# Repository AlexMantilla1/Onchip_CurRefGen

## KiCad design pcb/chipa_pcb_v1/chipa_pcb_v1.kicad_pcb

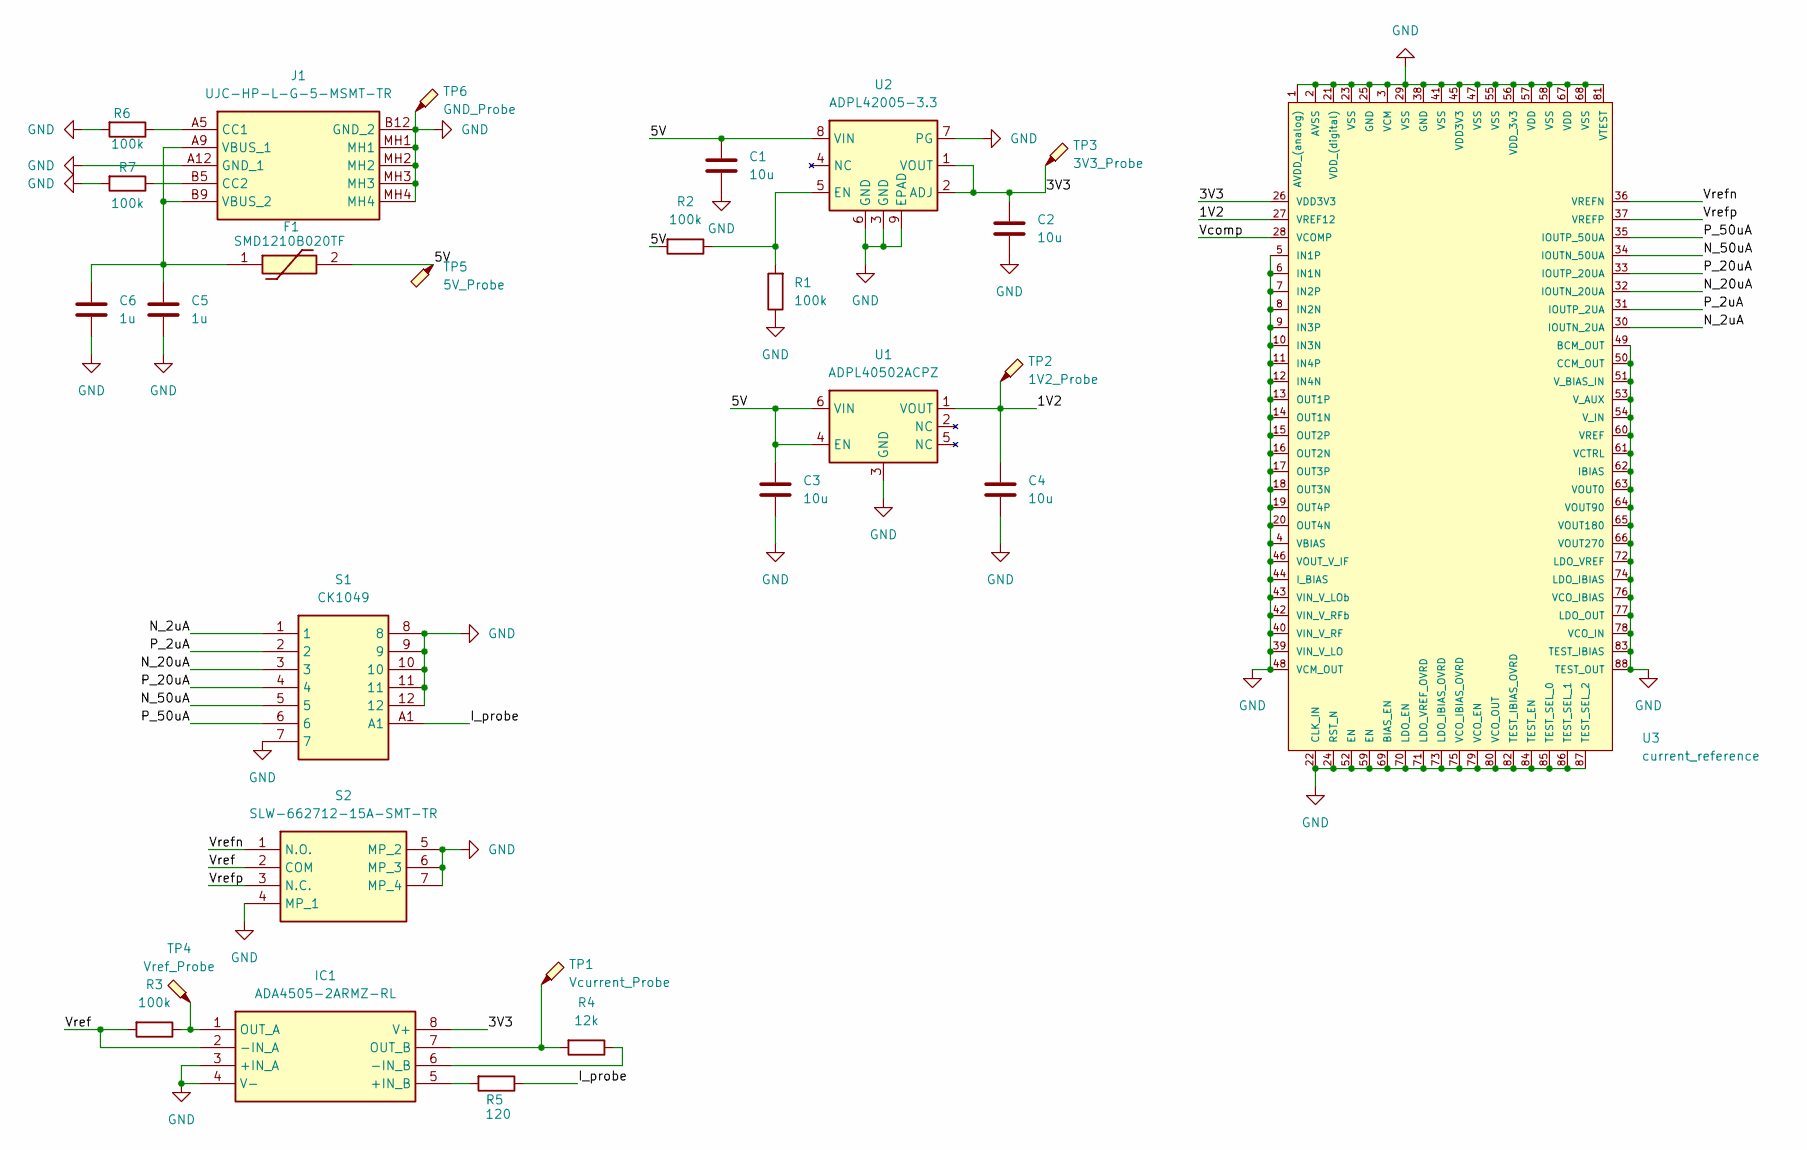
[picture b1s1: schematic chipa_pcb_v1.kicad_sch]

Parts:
C1, C2, C3, C4: 10u; C_0201_0603Metric
C5, C6: 1u; C_0201_0603Metric
F1: SMD1210B020TF; FUSC3226X110N; Mouser Part Number 603-SMD1210B020TF
IC1: ADA4505-2ARMZ-RL; SOP65P490X110-8N; Mouser Part Number 584-ADA4505-2ARMZ-R
J1: UJC-HP-L-G-5-MSMT-TR; UJCHPLG5MSMTTR; Mouser Part Number 179-UJCHPLG5MSMTTR
R1, R2, R3, R6, R7: 100k; R_0603_1608Metric
R4: 12k; R_0603_1608Metric
R5: 120; R_0603_1608Metric
S1: CK1049; CK1059; Mouser Part Number 105-CK1049
S2: SLW-662712-15A-SMT-TR; SLW66271215ASMTTR; Manufacturer_Part_Number SLW-662712-15A-SMT-TR
TP1: Vcurrent_Probe; TestPoint_Pad_4.0x4.0mm
TP2: 1V2_Probe; TestPoint_Pad_4.0x4.0mm
TP3: 3V3_Probe; TestPoint_Pad_4.0x4.0mm
TP4: Vref_Probe; TestPoint_Pad_4.0x4.0mm
TP5: 5V_Probe; TestPoint_Pad_4.0x4.0mm
TP6: GND_Probe; TestPoint_Pad_4.0x4.0mm
U1: ADPL40502ACPZ; LFCSP-6-1EP_2x2mm_P0.65mm_EP1x1.6mm
U2: ADPL42005-3.3; LFCSP-WD-8-1EP_3x3mm_P0.65mm_EP1.6x2.44mm
U3: current_reference; QFN-88_EP_10x10_Pitch0.4mm

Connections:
/1V2: C4.1, TP2.1 (1_1), U1.1 (VOUT), U3.27 (VREF12)
/3V3: C2.1, IC1.8 (V+), TP3.1 (1_1), U2.1 (VOUT), U2.2 (ADJ), U3.26 (VDD3V3)
/5V: C1.1, C3.1, F1.2, R2.2, TP5.1 (1_1), U1.4 (EN), U1.6 (VIN), U2.8 (VIN)
/I_probe: R5.1, S1.A1
/N_2uA: S1.1, U3.30 (IOUTN_2UA)
/N_20uA: S1.3, U3.32 (IOUTN_20UA)
/N_50uA: S1.5, U3.34 (IOUTN_50UA)
/P_2uA: S1.2, U3.31 (IOUTP_2UA)
/P_20uA: S1.4, U3.33 (IOUTP_20UA)
/P_50uA: S1.6, U3.35 (IOUTP_50UA)
/Vcomp: U3.28 (VCOMP)
/Vref: IC1.2 (-IN_A), R3.2, S2.2 (COM)
/Vrefn: S2.1 (N.O.), U3.36 (VREFN)
/Vrefp: S2.3 (N.C.), U3.37 (VREFP)
GND: C1.2, C2.2, C3.2, C4.2, C5.2, C6.2, IC1.3 (+IN_A), IC1.4 (V-), J1.A12 (GND_1), J1.B12 (GND_2), J1.MH1, J1.MH2, J1.MH3, J1.MH4, R1.1, R6.2, R7.2, S1.7, S1.8, S1.9, S1.10, S1.11, S1.12, S2.4 (MP_1), S2.5 (MP_2), S2.6 (MP_3), S2.7 (MP_4), TP6.1 (1_1), U1.3 (GND), U1.7 (GND), U2.3 (GND), U2.6 (GND), U2.7 (PG), U2.9 (EPAD), U3.1 (AVDD_(analog)), U3.2 (AVSS), U3.3 (VCM), U3.4 (VBIAS), U3.5 (IN1P), U3.6 (IN1N), U3.7 (IN2P), U3.8 (IN2N), U3.9 (IN3P), U3.10 (IN3N), U3.11 (IN4P), U3.12 (IN4N), U3.13 (OUT1P), U3.14 (OUT1N), U3.15 (OUT2P), U3.16 (OUT2N), U3.17 (OUT3P), U3.18 (OUT3N), U3.19 (OUT4P), U3.20 (OUT4N), U3.21 (VDD_(digital)), U3.22 (CLK_IN), U3.23 (VSS), U3.24 (RST_N), U3.25 (GND), U3.29 (VSS), U3.38 (GND), U3.39 (VIN_V_LO), U3.40 (VIN_V_RF), U3.41 (VSS), U3.42 (VIN_V_RFb), U3.43 (VIN_V_LOb), U3.44 (I_BIAS), U3.45 (VDD3V3), U3.46 (VOUT_V_IF), U3.47 (VSS), U3.48 (VCM_OUT), U3.49 (BCM_OUT), U3.50 (CCM_OUT), U3.51 (V_BIAS_IN), U3.52 (EN), U3.53 (V_AUX), U3.54 (V_IN), U3.55 (VSS), U3.56 (VDD_3v3), U3.57 (VDD), U3.58 (VSS), U3.59 (EN), U3.60 (VREF), U3.61 (VCTRL), U3.62 (IBIAS), U3.63 (VOUT0), U3.64 (VOUT90), U3.65 (VOUT180), U3.66 (VOUT270), U3.67 (VDD), U3.68 (VSS), U3.69 (BIAS_EN), U3.70 (LDO_EN), U3.71 (LDO_VREF_OVRD), U3.72 (LDO_VREF), U3.73 (LDO_IBIAS_OVRD), U3.74 (LDO_IBIAS), U3.75 (VCO_IBIAS_OVRD), U3.76 (VCO_IBIAS), U3.77 (LDO_OUT), U3.78 (VCO_IN), U3.79 (VCO_EN), U3.80 (VCO_OUT), U3.81 (VTEST), U3.82 (TEST_IBIAS_OVRD), U3.83 (TEST_IBIAS), U3.84 (TEST_EN), U3.85 (TEST_SEL_0), U3.86 (TEST_SEL_1), U3.87 (TEST_SEL_2), U3.88 (TEST_OUT)
unnamed: IC1.5 (+IN_B), R5.2
unnamed: IC1.6 (-IN_B), R4.1
unnamed: IC1.1 (OUT_A), R3.1, TP4.1 (1_1)
unnamed: IC1.7 (OUT_B), R4.2, TP1.1 (1_1)
unnamed: J1.A5 (CC1), R6.1
unnamed: J1.B5 (CC2), R7.1
unnamed: C5.1, C6.1, F1.1, J1.A9 (VBUS_1), J1.B9 (VBUS_2)
unnamed: R1.2, R2.1, U2.5 (EN)

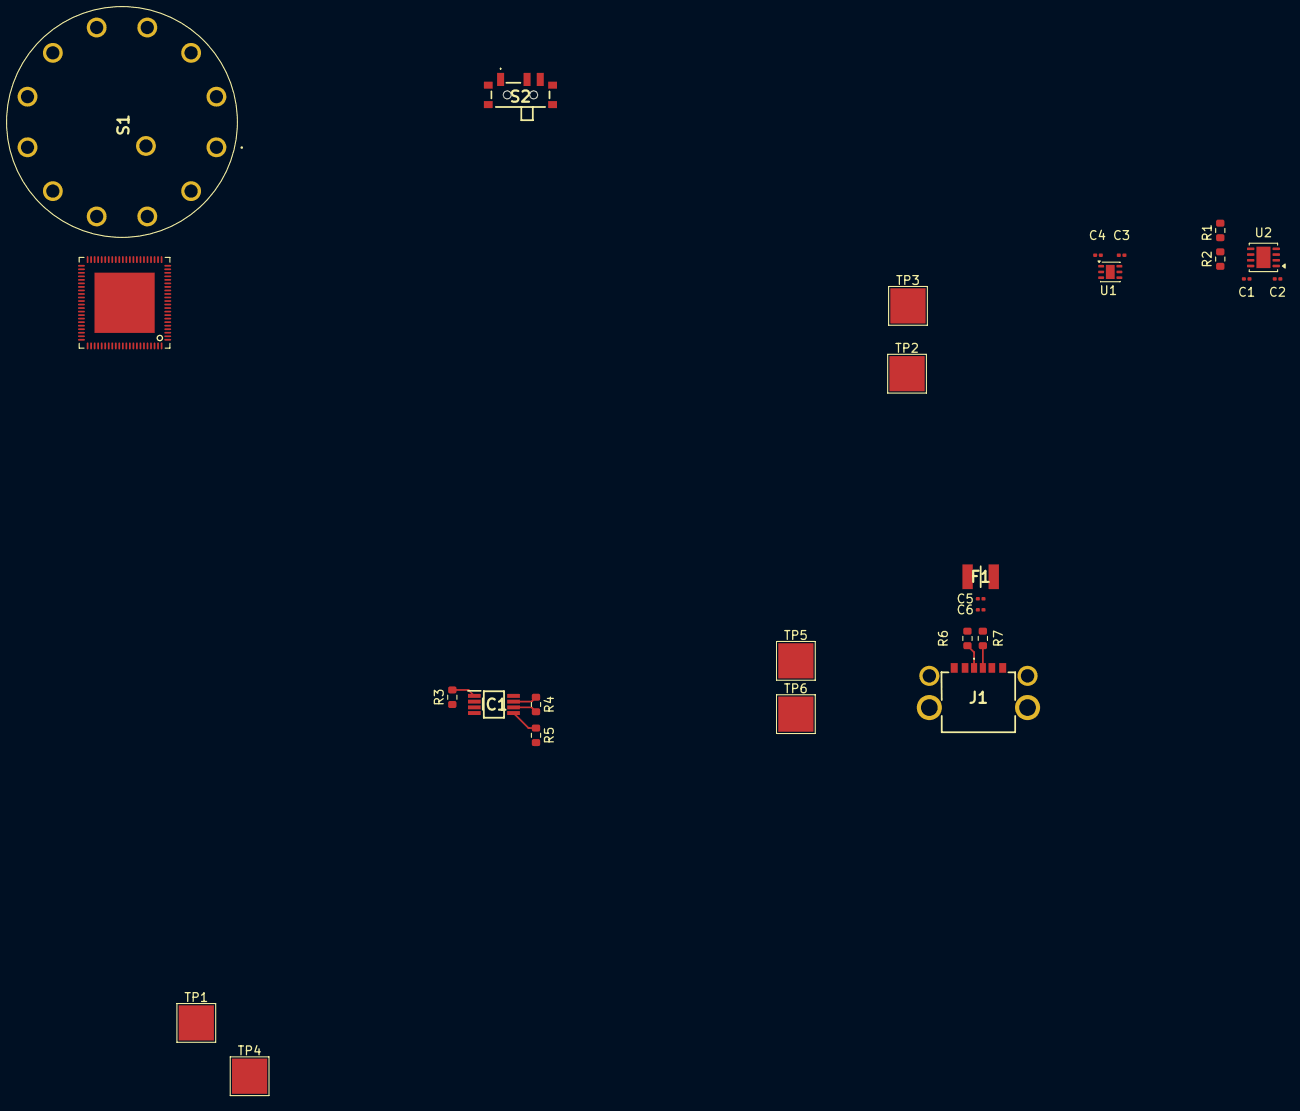
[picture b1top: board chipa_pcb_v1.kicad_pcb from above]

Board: 2 copper layers, 27 parts (0 on the bottom side), 22 nets.
